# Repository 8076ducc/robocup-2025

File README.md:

# ducc. Robotics: RoboCupJunior Soccer 2025

This repository contains ducc's working files and source code for the 2025 RoboCupJunior Soccer Open and Soccer Lightweight competition.

## About

ducc is a six-man team comprising **Neo Hao Jun, Isaac Tan, Zhu Yunsong, Aidan Yeong, Faith Yang and Neo Jun Hao** from the **Hwa Chong Robotics Club** in Singapore.

## Technologies

This project was built with the following tools:

- Mechanical: Autodesk Fusion
- Electrical: KiCad 7.0
- Programming: PlatformIO

## Intellectual Property

### Copyright

© 2025, ducc. Robotics Competition Team.

While we have made every effort to abide by legal and ethical requirements when using works that we did not create, some may have been overlooked inadvertently. Please let us know and we will be happy to make the necessary arrangements.

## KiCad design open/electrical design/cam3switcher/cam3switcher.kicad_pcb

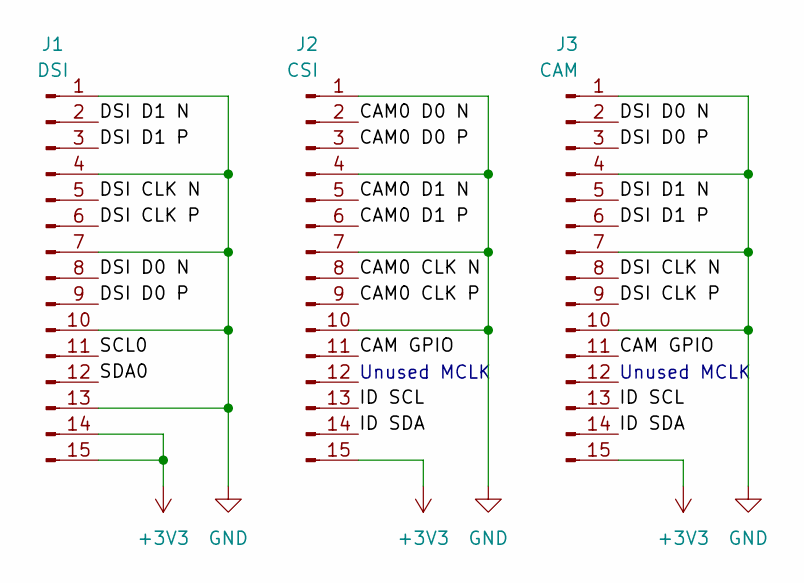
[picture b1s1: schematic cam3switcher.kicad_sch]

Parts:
J1: DSI; TE_1-84952-5_1x15-1MP_P1.0mm_Horizontal
J2: CSI; TE_1-84952-5_1x15-1MP_P1.0mm_Horizontal
J3: CAM; TE_1-84952-5_1x15-1MP_P1.0mm_Horizontal

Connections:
+3V3: J1.14, J1.15, J2.15, J3.15
/CAM0 CLK N: J2.8
/CAM0 CLK P: J2.9
/CAM0 D0 N: J2.2
/CAM0 D0 P: J2.3
/CAM0 D1 N: J2.5
/CAM0 D1 P: J2.6
/CAM GPIO: J2.11, J3.11
/DSI CLK N: J1.5, J3.8
/DSI CLK P: J1.6, J3.9
/DSI D0 N: J1.8, J3.2
/DSI D0 P: J1.9, J3.3
/DSI D1 N: J1.2, J3.5
/DSI D1 P: J1.3, J3.6
/ID SCL: J2.13, J3.13
/ID SDA: J2.14, J3.14
/SCL0: J1.11
/SDA0: J1.12
GND: J1.1, J1.4, J1.7, J1.10, J1.13, J2.1, J2.4, J2.7, J2.10, J3.1, J3.4, J3.7, J3.10

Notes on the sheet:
Unused MCLK

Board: 2 copper layers, 3 parts (0 on the bottom side), 11 nets, no tracks yet.

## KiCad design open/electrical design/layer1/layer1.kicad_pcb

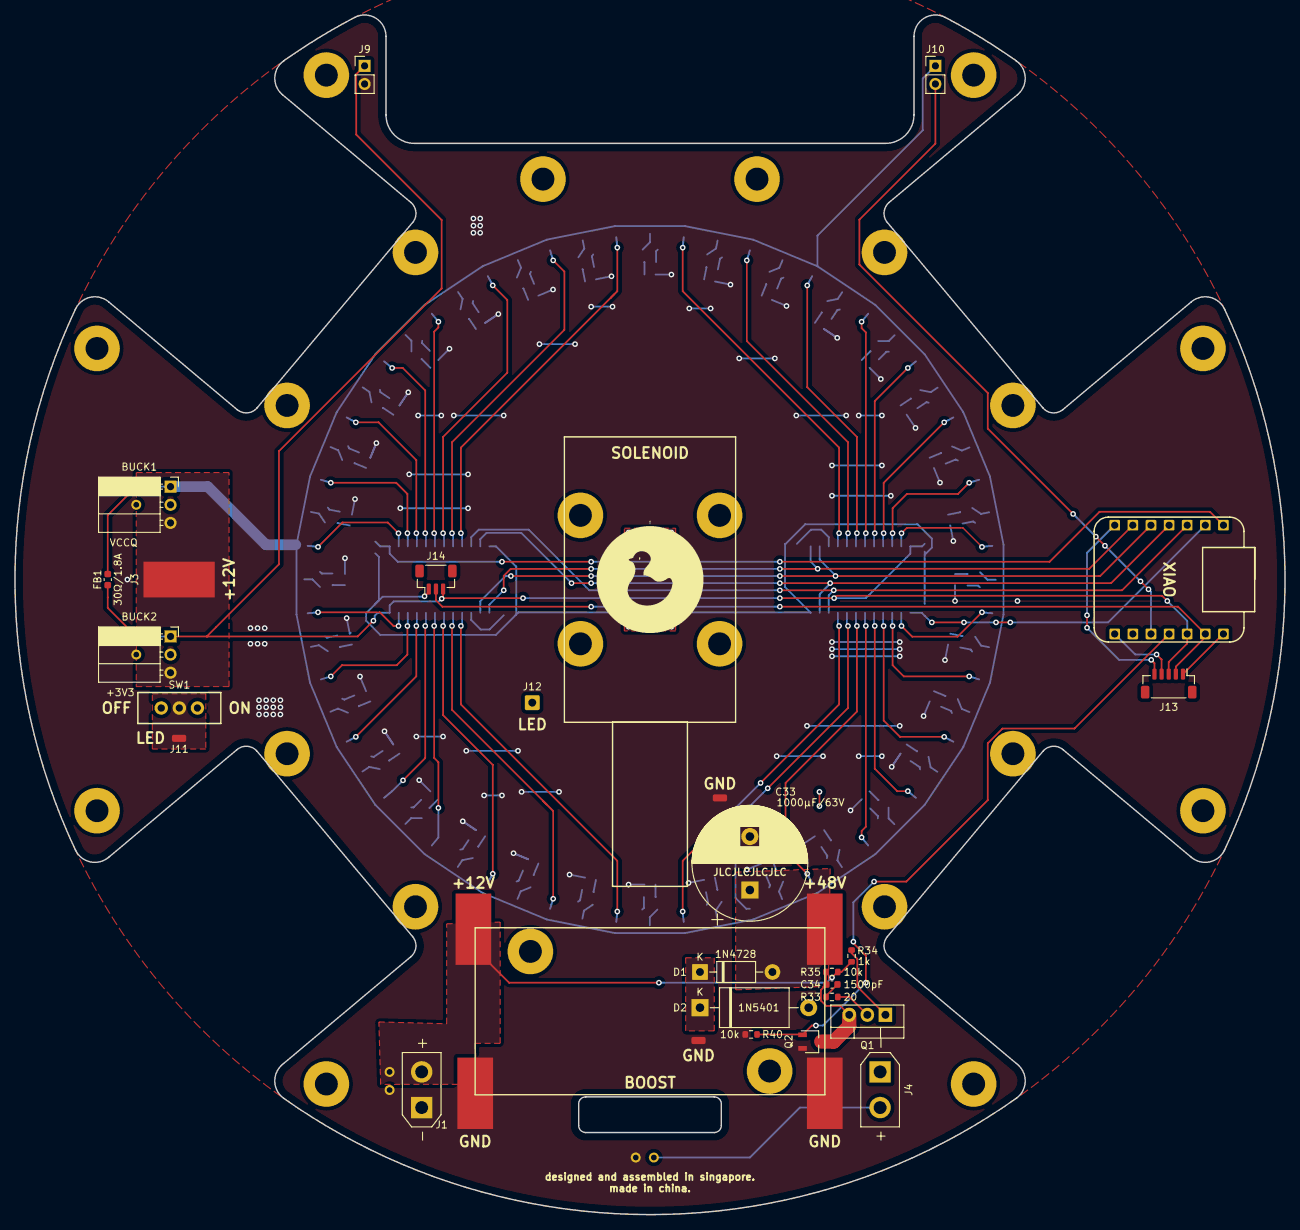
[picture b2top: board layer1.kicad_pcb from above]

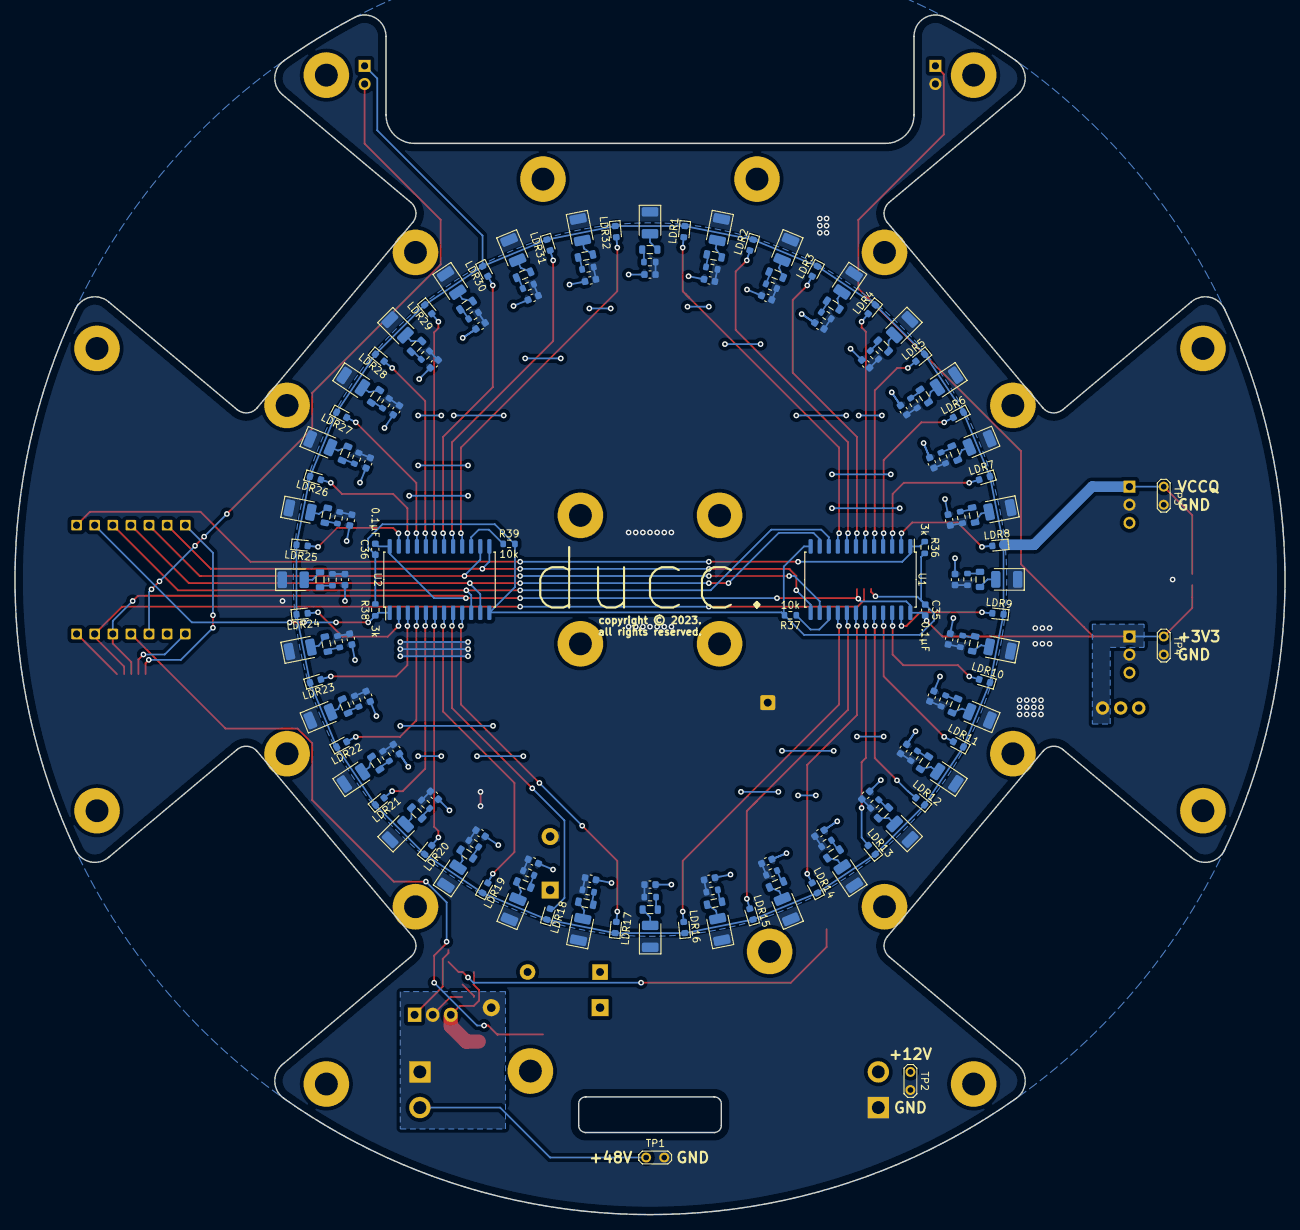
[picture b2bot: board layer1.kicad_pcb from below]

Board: 2 copper layers, 178.0 x 168.1 mm, 226 parts (172 on the bottom side), 122 nets.

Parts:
BUCK1: VCCQ; PinSocket_1x03_P2.54mm_Horizontal
BUCK2: +3V3; PinSocket_1x03_P2.54mm_Horizontal
C1, C2, C3, C4, C5, C6, C7, C8, C9, C10, C11, C12, C13, C14, C15, C16, C17, C18, C19, C20, C21, C22, C23, C24, C25, C26, C27, C28, C29, C30, C31, C32: 1uF; C_0603_1608Metric
C33: 1000µF/63V; CP_Radial_D16.0mm_P7.50mm
C34: 1500pF; C_0603_1608Metric
C35, C36: 0.1μF; C_0603_1608Metric
D1: 1N4728; D_DO-41_SOD81_P10.16mm_Horizontal
D2: 1N5401; D_DO-27_P15.24mm_Horizontal
FB1: 30Ω/1.8A; C_0603_1608Metric
H1, H2, H3, H4, H5, H6, H7, H8, H9, H10, H11, H12, H13, H14, H15, H16, H17, H18, H19, H20, H21, H22, H23, H24: MountingHole; MountingHole_3.2mm_M3_Pad
J1: XT30-F; AMASS_XT30UPB-F_1x02_P5.0mm_Vertical
J2, J11, J15: Conn_01x01_Socket; SolderWirePad_1x01_SMD_1x2mm
J3, J5, J6, J7, J8: Conn_01x01_Socket; SolderWirePad_1x01_SMD_5x10mm
J4: XT30PW-F; AMASS_XT30UPB-F_1x02_P5.0mm_Vertical
J9, J10: Conn_01x02_Pin; PinHeader_1x02_P2.54mm_Vertical
J12: Conn_01x01_Socket; SolderWire-0.5sqmm_1x01_D0.9mm_OD2.1mm
J13: SH1.0 5P; JST_SH_BM05B-SRSS-TB_1x05-1MP_P1.00mm_Vertical
J14: SH1.0 3P; JST_SH_BM03B-SRSS-TB_1x03-1MP_P1.00mm_Vertical
L1, L2, L3, L4, L5, L6, L7, L8, L9, L10, L11, L12, L13, L14, L15, L16, L17, L18, L19, L20, L21, L22, L23, L24, L25, L26, L27, L28, L29, L30, L31, L32: 10µH; L_0805_2012Metric
LDR1, LDR2, LDR3, LDR4, LDR5, LDR6, LDR7, LDR8, LDR9, LDR10, LDR11, LDR12, LDR13, LDR14, LDR15, LDR16, LDR17, LDR18, LDR19, LDR20, LDR21, LDR22, LDR23, LDR24, LDR25, LDR26, LDR27, LDR28, LDR29, LDR30, LDR31, LDR32: ALS-PT19-315C; D_0603_1608Metric
LED1, LED2, LED3, LED4, LED5, LED6, LED7, LED8, LED9, LED10, LED11, LED12, LED13, LED14, LED15, LED16, LED17, LED18, LED19, LED20, LED21, LED22, LED23, LED24, LED25, LED26, LED27, LED28, LED29, LED30, LED31, LED32: WHITE 3528; CP_EIA-3528-12_Kemet-T
Q1: MOSFET-NCH-FQP30N06L; TO-220-3_Vertical
Q2: MOSFET-NCH-AO3404A; TSOT-23
R1, R2, R3, R4, R5, R6, R7, R8, R9, R10, R11, R12, R13, R14, R15, R16, R17, R18, R19, R20, R21, R22, R23, R24, R25, R26, R27, R28, R29, R30, R31, R32: 0R39; R_0603_1608Metric
R33: 20; R_0603_1608Metric
R34: 1k; R_0603_1608Metric
R35, R37, R39, R40: 10k; R_0603_1608Metric
R36, R38: 3k; R_0603_1608Metric
SW1: SW_SPDT; SWITCH_SPDT_PTH_11.6X4.0MM
TP1, TP2, TP3, TP4: TestPoint_2Pole; TestPoint_2Pads_Pitch2.54mm_Drill0.8mm
U1, U2: CD74HC4067SM; SOIC-24W_7.5x15.4mm_P1.27mm
U3: MOUDLE-SEEEDUINO-XIAO-ESP32C3; xiao-esp32c3

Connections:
+3V3: BUCK2.1, C35.1, C36.1, FB1.1, J9.1, J13.3, J14.3, SW1.1 (A), TP4.1, U1.24 (VCC), U2.24 (VCC), U3.12 (3V3)
+5V: J13.1, U3.14 (5V)
+12V: BUCK1.3, BUCK2.3, J1.2, J3.1, J5.1, R34.1, R35.1, TP2.1
+48V: C33.1, D1.2 (A), J4.2, J7.1, TP1.1
/BALL: J10.2, U3.10 (PA5_A9_D9_MISO)
/LED: C1.1, C2.1, C3.1, C4.1, C5.1, C6.1, C7.1, C8.1, C9.1, C10.1, C11.1, C12.1, C13.1, C14.1, C15.1, C16.1, C17.1, C18.1, C19.1, C20.1, C21.1, C22.1, C23.1, C24.1, C25.1, C26.1, C27.1, C28.1, C29.1, C30.1, C31.1, C32.1, J11.1, J12.1, R1.1, R2.1, R3.1, R4.1, R5.1, R6.1, R7.1, R8.1, R9.1, R10.1, R11.1, R12.1, R13.1, R14.1, R15.1, R16.1, R17.1, R18.1, R19.1, R20.1, R21.1, R22.1, R23.1, R24.1, R25.1, R26.1, R27.1, R28.1, R29.1, R30.1, R31.1, R32.1, SW1.2 (B)
/MUX1OUT: R36.1, U1.1 (COM), U3.1 (PA02_A0_D0)
/MUX2OUT: R38.1, U2.1 (COM), U3.2 (PA4_A1_D1)
/RX: J13.4, U3.8 (PB09_A7_D7_RX)
/S0: U1.10 (S0), U2.10 (S0), U3.3 (PA10_A2_D2)
/S1: U1.11 (S1), U2.11 (S1), U3.4 (PA11_A3_D3)
/S2: U1.14 (S2), U2.14 (S2), U3.5 (PA8_A4_D4_SDA)
/S3: U1.13 (S3), U2.13 (S3), U3.6 (PA9_A5_D5_SCL)
/SOLENOIDON: Q2.1 (G), R40.1, U3.11 (PA6_A10_D10_MOSI)
/TX: J13.5, U3.7 (PB08_A6_D6_TX)
GND: BUCK1.2, BUCK2.2, C1.2, C2.2, C3.2, C4.2, C5.2, C6.2, C7.2, C8.2, C9.2, C10.2, C11.2, C12.2, C13.2, C14.2, C15.2, C16.2, C17.2, C18.2, C19.2, C20.2, C21.2, C22.2, C23.2, C24.2, C25.2, C26.2, C27.2, C28.2, C29.2, C30.2, C31.2, C32.2, C33.2, J1.1, J2.1, J6.1, J8.1, J9.2, J15.1, LED1.1 (K), LED2.1 (K), LED3.1 (K), LED4.1 (K), LED5.1 (K), LED6.1 (K), LED7.1 (K), LED8.1 (K), LED9.1 (K), LED10.1 (K), LED11.1 (K), LED12.1 (K), LED13.1 (K), LED14.1 (K), LED15.1 (K), LED16.1 (K), LED17.1 (K), LED18.1 (K), LED19.1 (K), LED20.1 (K), LED21.1 (K), LED22.1 (K), LED23.1 (K), LED24.1 (K), LED25.1 (K), LED26.1 (K), LED27.1 (K), LED28.1 (K), LED29.1 (K), LED30.1 (K), LED31.1 (K), LED32.1 (K), Q2.2 (S), R40.2, TP1.2, TP2.2, TP3.2, TP4.2
GNDA: C35.2, C36.2, J14.1, R36.2, R37.2, R38.2, R39.2, U1.12 (GND), U2.12 (GND)
GNDD: J13.2, J14.2, U3.13 (GND)
unnamed: C34.1, R33.2
unnamed: D1.1 (K), D2.1 (K)
unnamed: D2.2 (A), J4.1, Q1.2 (D), R33.1
unnamed: L1.2, R1.2
unnamed: L2.2, R2.2
unnamed: L3.2, R3.2
unnamed: L4.2, R4.2
unnamed: L5.2, R5.2
unnamed: L6.2, R6.2
unnamed: L7.2, R7.2
unnamed: L8.2, R8.2
unnamed: L9.2, R9.2
unnamed: L10.2, R10.2
unnamed: L11.2, R11.2
unnamed: L12.2, R12.2
unnamed: L13.2, R13.2
unnamed: L14.2, R14.2
unnamed: L15.2, R15.2
unnamed: L16.2, R16.2
unnamed: L17.2, R17.2
unnamed: L18.2, R18.2
unnamed: L19.2, R19.2
unnamed: L20.2, R20.2
unnamed: L21.2, R21.2
unnamed: L22.2, R22.2
unnamed: L23.2, R23.2
unnamed: L24.2, R24.2
unnamed: L25.2, R25.2
unnamed: L26.2, R26.2
unnamed: L27.2, R27.2
unnamed: L28.2, R28.2
unnamed: L29.2, R29.2
unnamed: L30.2, R30.2
unnamed: L31.2, R31.2
unnamed: L32.2, R32.2
unnamed: L1.1, LED1.2 (A)
unnamed: L2.1, LED2.2 (A)
unnamed: L3.1, LED3.2 (A)
unnamed: L4.1, LED4.2 (A)
unnamed: L5.1, LED5.2 (A)
unnamed: L6.1, LED6.2 (A)
unnamed: L7.1, LED7.2 (A)
unnamed: L8.1, LED8.2 (A)
unnamed: L9.1, LED9.2 (A)
unnamed: L10.1, LED10.2 (A)
unnamed: L11.1, LED11.2 (A)
unnamed: L12.1, LED12.2 (A)
unnamed: L13.1, LED13.2 (A)
unnamed: L14.1, LED14.2 (A)
unnamed: L15.1, LED15.2 (A)
unnamed: L16.1, LED16.2 (A)
unnamed: L17.1, LED17.2 (A)
unnamed: L18.1, LED18.2 (A)
unnamed: L19.1, LED19.2 (A)
unnamed: L20.1, LED20.2 (A)
unnamed: L21.1, LED21.2 (A)
unnamed: L22.1, LED22.2 (A)
unnamed: L23.1, LED23.2 (A)
unnamed: L24.1, LED24.2 (A)
unnamed: L25.1, LED25.2 (A)
unnamed: L26.1, LED26.2 (A)
unnamed: L27.1, LED27.2 (A)
unnamed: L28.1, LED28.2 (A)
unnamed: L29.1, LED29.2 (A)
unnamed: L30.1, LED30.2 (A)
unnamed: L31.1, LED31.2 (A)
unnamed: L32.1, LED32.2 (A)
unnamed: Q1.1 (G), R34.2
unnamed: C34.2, Q1.3 (S), Q2.3 (D), R35.2
unnamed: LDR1.2, U1.9 (I0)
unnamed: LDR2.2, U1.8 (I1)
unnamed: LDR3.2, U1.7 (I2)
unnamed: LDR4.2, U1.6 (I3)
unnamed: LDR5.2, U1.5 (I4)
unnamed: LDR6.2, U1.4 (I5)
unnamed: LDR7.2, U1.3 (I6)
unnamed: LDR8.2, U1.2 (I7)
unnamed: LDR9.2, U1.23 (I8)
unnamed: LDR10.2, U1.22 (I9)
unnamed: LDR11.2, U1.21 (I10)
unnamed: LDR12.2, U1.20 (I11)
unnamed: LDR13.2, U1.19 (I12)
unnamed: LDR14.2, U1.18 (I13)
unnamed: LDR15.2, U1.17 (I14)
unnamed: LDR16.2, U1.16 (I15)
unnamed: R37.1, U1.15 (~E)
unnamed: LDR17.2, U2.9 (I0)
unnamed: LDR18.2, U2.8 (I1)
unnamed: LDR19.2, U2.7 (I2)
unnamed: LDR20.2, U2.6 (I3)
unnamed: LDR21.2, U2.5 (I4)
unnamed: LDR22.2, U2.4 (I5)
unnamed: LDR23.2, U2.3 (I6)
unnamed: LDR24.2, U2.2 (I7)
unnamed: LDR25.2, U2.23 (I8)
unnamed: LDR26.2, U2.22 (I9)
unnamed: LDR27.2, U2.21 (I10)
unnamed: LDR28.2, U2.20 (I11)
unnamed: LDR29.2, U2.19 (I12)
unnamed: LDR30.2, U2.18 (I13)
unnamed: LDR31.2, U2.17 (I14)
unnamed: LDR32.2, U2.16 (I15)
unnamed: R39.1, U2.15 (~E)
VCCQ: BUCK1.1, FB1.2, J10.1, LDR1.1, LDR2.1, LDR3.1, LDR4.1, LDR5.1, LDR6.1, LDR7.1, LDR8.1, LDR9.1, LDR10.1, LDR11.1, LDR12.1, LDR13.1, LDR14.1, LDR15.1, LDR16.1, LDR17.1, LDR18.1, LDR19.1, LDR20.1, LDR21.1, LDR22.1, LDR23.1, LDR24.1, LDR25.1, LDR26.1, LDR27.1, LDR28.1, LDR29.1, LDR30.1, LDR31.1, LDR32.1, TP3.1

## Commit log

2024-10-29 rename folder lw 2024
2024-10-29 tt interface font
2024-10-29 rename dir
2024-12-26 parts
2024-12-31 mech design stuff
2024-12-31 ducc shirt
2025-01-01 rename shirt file to 2025
2025-01-07 screw drawing
2025-01-07 nuts
2025-01-08 my balls itch daddy
2025-01-11 moved ducc shirt assets to branding repo
2025-01-22 22/01
2025-02-01 skinbidi
2025-02-01 edit folder names
2025-02-01 patch missing software files
2025-02-01 update .pio files
2025-02-01 some 3mf files and switcherboard schema
2025-02-01 minor changes to switcher board
2025-02-01 switcher board router i2c of camera to csi i2c lanes
2025-02-07 rpi files from cm5
2025-02-07 service files, changed raspi-gpio to pinctrl in configure gpio service for cm5, as raspi-gpio is no longer supported; disabled show debug windows in threads.h
2025-02-07 toggle show debug windows to falase
2025-02-12 add .pio/build to .gitignore
2025-02-12 update .gitignore to exclude all files in .pio/build directory
2025-02-12 Ignore .pio/build folder
2025-02-15 removed all references of Lidar
2025-02-20 rpi code from cm5 A
2025-02-21 Add new 3D models and remove obsolete files from mechanical design
2025-02-22 rename lidar.cpp to camera.cpp
2025-02-22 resolve merge conflicts
2025-02-22 make some changes
2025-02-22 have to reregress in mm to make localisation work
2025-02-22 code from cm5
2025-02-25 try to fix local, dk if works @isaac
2025-02-25 issue: regression for goals are ass
2025-02-25 have to do regerssion for goal
2025-02-25 regress for blue and yellow functions premade
2025-02-26 try to use pixel distance to compute distance from cneter using a ratio rather than regression
2025-02-26 Add debugging output for yellow and blue goal positions in camera pose TODO: check threshold again
2025-02-27 Update mechanical design files, new mirror drawings
2025-02-27 layer 4 dxf new
2025-02-27 some mech stuff
2025-02-28 Update master.3mf file in mechanical design
2025-02-28 regression new algo
2025-02-28 changed coefficients for backwards regression
2025-02-28 regression can go kys
2025-03-03 mech stuff
2025-03-03 remove lidar reference
2025-03-03 remove unused storing data
2025-03-03 comment unused ball regression
2025-03-03 comment out debug print statements in algorithm and serial files
2025-03-03 im gonna lose it why tf does imu serial not work
2025-03-03 added 2 lines from 2024 code
2025-03-03 update 3D model files for mechanical design
2025-03-04 get IMU to send serial (temporary fix)
2025-03-04 add payload size validation and improve debug logging in serial handling
2025-03-04 non critical
2025-03-04 add payload size validation and improve error logging in serial handling
2025-03-04 remove unused lidar functions and improve payload size validation in serial handling
2025-03-04 refactor: clean up serial handling code and improve readability
2025-03-04 testing light gate
2025-03-05 enhance error logging for invalid payload size in serial handling
2025-03-05 improve error logging for invalid payload size in serial handling
2025-03-05 fix: reduce camera serial baud rate to 500k
2025-03-05 change baud rate to 500k in rpi
2025-03-05 fix: enhance error logging for invalid payload sizes in IMU and Teensy data handling
2025-03-05 code clean up
2025-03-05 remove lidar refs
2025-03-05 fix: update camera serial baud rate comment for clarity
2025-03-06 fix: correct logging statement for IMU bearing data and add todo comment for serial condition
2025-03-06 fix: adjust distance calculations for ball orbiting behavior
2025-03-06 feat: add new DXF file for mechanical design layer 4 and 5
2025-03-06 l1 debug
2025-03-06 fix lower camera baudrate to 500k (l1 to teensy1 works now)
2025-03-06 update ball threshold value for 2025 lightgate
2025-03-07 refactor serial communication settings and improve debug output for camera data
2025-03-07 increase teensy1 serial baud rate from 1M to 2M for improved communication
2025-03-07 moved camera serial receiving to teensy1
2025-03-09 rename getSingleCameraPose to storeSingleCameraPose for consistency
2025-03-09 add new DXF file for layer 5.1 and update layer 5
2025-03-09 comment out some stuff
2025-03-09 rename BOT1 to BOT_1 for consistency in main.h
2025-03-09 tuned orbit and added exponential acceleration and deceleration to orbitToBall
2025-03-09 rename BOT_1 to BOT_A (all instances)
2025-03-10 enable serial debug messages and update LDR thresholds
2025-03-10 update nut hole tester design file
2025-03-10 rpi code from cm5a
2025-03-10 update light ring thresholds, calibrate bot b threshold for lighring
2025-03-10 Revert to commit 2434547
2025-03-10 Rename BOT1 to BOT_A and update related configurations in Bluetooth and light ring modules
2025-03-12 Update light ring thresholds, adjust ball threshold, and enhance camera pose calculations
2025-03-12 Refactor storeCameraPose function to simplify pose calculations and remove commented-out code
2025-03-12 write code to slow down bot when near edges (not tested)
2025-03-12 Refactor striker function to simplify task assignments and remove commented-out code
2025-03-12 Replace orbitToBall call with striker function in main loop
2025-03-12 Adjust speed control logic in orbitScore function based on goal distance
2025-03-12 Refactor orbitToBall and orbitScore functions for improved speed control and clarity
2025-03-12 bunch of mech changes
2025-03-12 Add detected flag to Goal struct for tracking goal detection status
2025-03-12 Update goal detection logic to use struct flags for yellow and blue goals
2025-03-12 Replace min with fmin for velocity and angular velocity clamping
2025-03-12 tune orbit and edge decel
2025-03-12 stop humping the line if ball is in the goal/unreachable already
2025-03-12 (doesnt work yet) added a counter system to continue orbitToScore if the ball comes out of the catchment for a while only
2025-03-13 added tune comment
2025-03-13 added x-axis threshold to prevent stalling when bot thinks ball is in goal but its not (still need to test)
2025-03-13 experimental goalie code for intercepting striker
2025-03-14 refactor defendGoal and soloGoalie functions for improved ball detection and handling
2025-03-14 refactor goalie logic for enhanced ball interception and tracking
2025-03-14 update cover front design in layer 1
2025-03-14 ``` refactor goalie logic for enhanced ball interception and tracking ```
2025-03-14 remove commented-out code for striker and loop functions to improve readability
2025-03-14 refactor bound function parameters for clarity
2025-03-14 refactor speed calculations to use bound function for improved clarity and consistency
2025-03-14 refactor bound function parameters for consistency and add xyToBearing function for angle calculation
2025-03-14 (to test) goalie code for bot to follow ball in x direction
2025-03-14 use millis to set timer
2025-03-14 update mechanical design file with new specifications
2025-03-16 update catchment area cover
2025-03-16 code cleanujp
2025-03-16 fix: correct bearing calculation in xyToBearing function
2025-03-16 goalie track ball x
2025-03-16 fix: adjust ball threshold
2025-03-16 fix striker code not working (goal y was declared outside of functions and does not get updated)
2025-03-17 fix: reduce catchment timeout and improve striker task handling
2025-03-17 feat: add new kicker slide design and update existing mechanical components
2025-03-17 feat: implement goalie tracking and rushing functionality
2025-03-17 added back payload size check from cam to teensy1
2025-03-17 feat: update mechanical design files for kicker components
2025-03-18 feat: refactor camera pose handling and update method names for clarity
2025-03-18 remove old unused regression functions
2025-03-18 feat: add methods to store open goal poses and update camera pose handling
2025-03-18 feat: rename camera pose methods to goal pose for consistency
2025-03-18 changed to score on empty area of the goal
2025-03-18 atan2 does the same shit as xytobearing
2025-03-19 revert to xyToBearing function and update target_angle calculations
2025-03-19 kicker stuff
2025-03-19 chore: update mechanical design files for kicker components
2025-03-19 debug time taken to send serial from cam
2025-03-19 tune: adjust goalie tracking speed parameters
2025-03-19 tune: adjust scoring behavior and timeout parameters
2025-03-19 tune: enhance goalie behavior for ball tracking and line rejection
2025-03-21 tune: adjust goalie tracking parameters and implement PID control for speed
2025-03-22 many code changes
2025-03-22 many mech changes
2025-03-22 updated code from cm5-a
2025-03-25 added a function for movetopoint
2025-03-25 update: modify spur gear and master design files
2025-03-25 regression localisation code
2025-03-26 added regression
2025-03-26 added regression calculation for ball distance
2025-03-26 update: adjust serial baud rates, refine orbiting algorithm
2025-03-27 mech stuffs
2025-03-27 storeRobotPose update to consider cases where only one goal is deteced
2025-03-27 mech
2025-03-28 updated regression for the new mirror
2025-03-28 fix serial and regression for orbit
2025-03-28 cm5a code
2025-03-28 introduce autosave functionality for calibration
2025-03-29 fix issues with autosave
2025-03-29 remove requirement to end program to save data
2025-03-29 fix a bunch of syntax errors
2025-03-29 update executables
2025-03-29 resolve conflicting colour thresholds
2025-03-29 modified window size to 864
2025-03-29 tune calibration values
2025-03-29 refactor code, purge all serial read
2025-03-29 changed a lot of shit
2025-03-29 clean up
2025-03-29 big load of mech stuff baby
2025-03-31 changed goalie code
2025-03-31 reduce threshold for kalman predictor
2025-03-31 remove getNewImage from threading
2025-03-31 increase overall fps to 120
2025-03-31 revert to old code, convert to 450x450 frame
2025-04-01 scale goal and pose coordinates by window scale factor (x1.92)
2025-04-01 mech new kicker
2025-04-02 changed regressed values
2025-04-02 reverted back to working cm5 code to patch missing sliders bug
2025-04-04 added goalie stuff and tuned orbit and
2025-04-04 Enable debug mode and adjust ball threshold; refactor kicker servo logic for improved timing and control
2025-04-04 overnight
2025-04-05 Add ball_last_seen to Ball struct; adjust ball threshold and tuning parameters
2025-04-05 KICKER WORKS
2025-06-07 last of the remaining changes from cup '25

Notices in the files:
open/electrical design/layer1/layer1.kicad_pcb:
copyright © 2023.
all rights reserved.
